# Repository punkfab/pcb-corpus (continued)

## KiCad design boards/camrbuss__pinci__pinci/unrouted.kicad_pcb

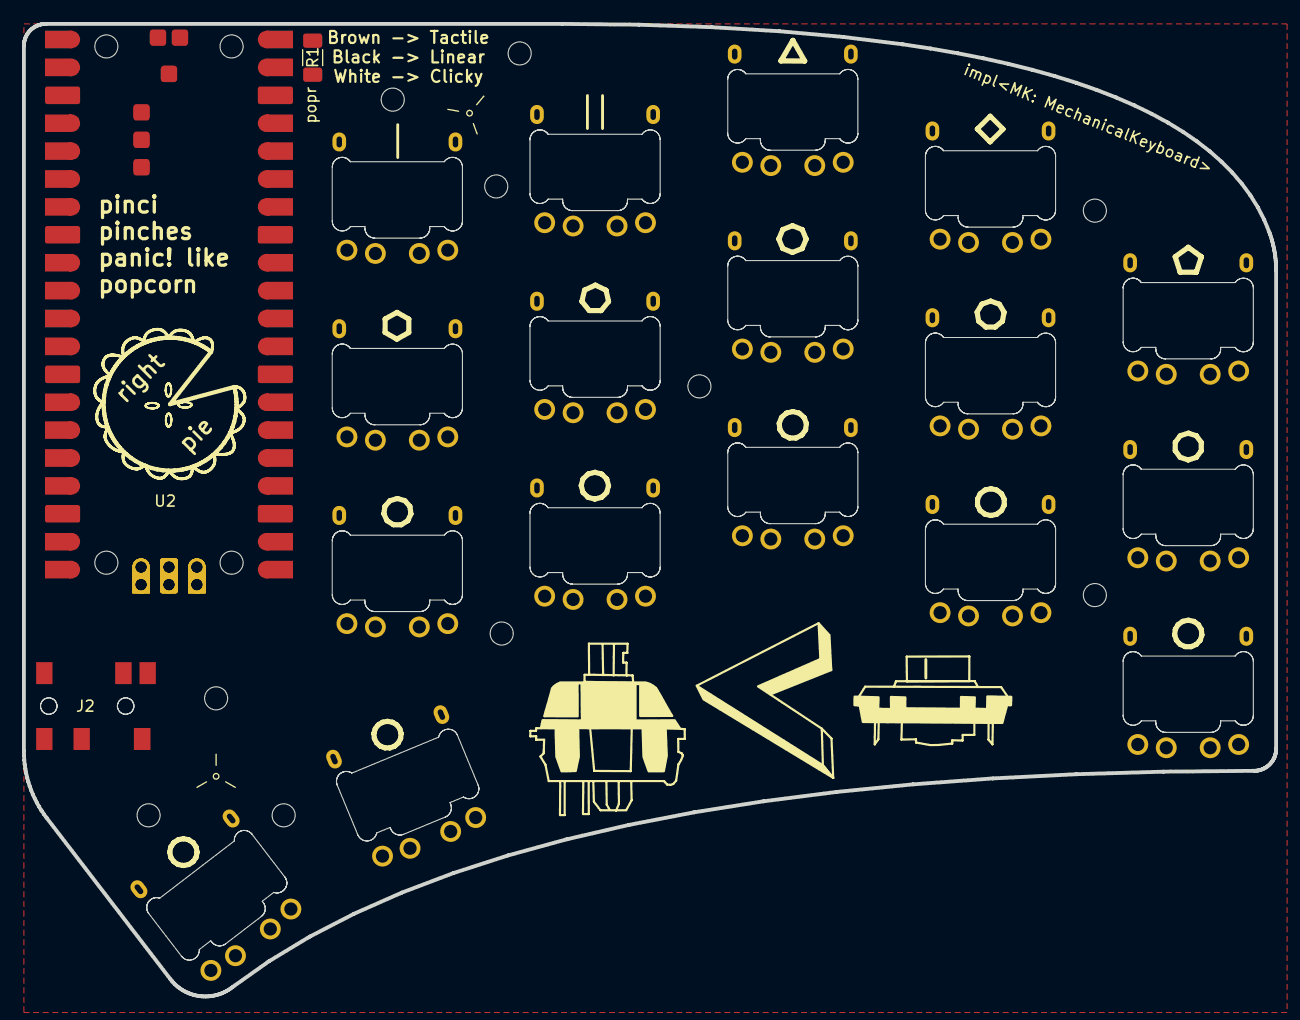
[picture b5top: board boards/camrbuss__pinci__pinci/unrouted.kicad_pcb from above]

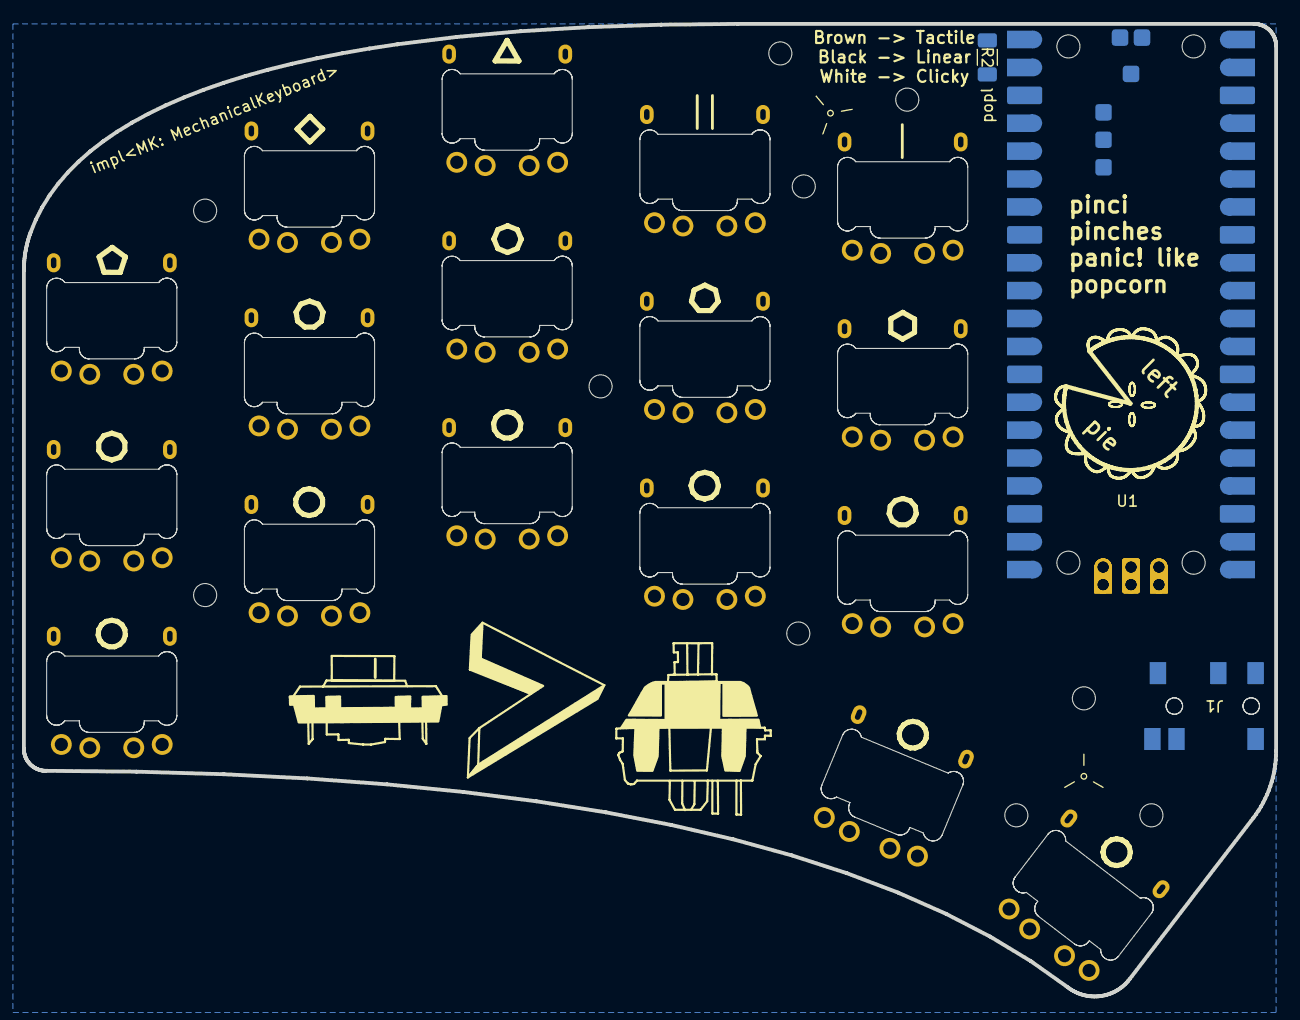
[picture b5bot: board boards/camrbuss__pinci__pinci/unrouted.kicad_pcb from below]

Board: 2 copper layers, 114.0 x 88.5 mm, 29 parts (5 on the bottom side), 42 nets, no tracks yet.

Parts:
H1, H2: MountingHole; 90611A112_Screw_Mount_Nut
H3, H4, H5, H6: MountingHole; M2_Hole
J1, J2: AudioJack4; TRRS_Socket_54-00177
R1, R2: 10k; R_1206_3216Metric_Pad1.30x1.75mm_HandSolder
SW1, SW2, SW3, SW4, SW5, SW6, SW7, SW8, SW9, SW10, SW11, SW12, SW13, SW14, SW15, SW16, SW17: SW_Push_Dual; Kailh_PG1232
U1, U2: PICO; raspberrypi_pico

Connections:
+3V3: R1.2, U1.36 (3V3), U2.36 (3V3)
GND: J1.T, J2.T, R2.1, SW1.2, SW1.4, SW2.2, SW2.4, SW3.2, SW3.4, SW4.2, SW4.4, SW5.2, SW5.4, SW6.2, SW6.4, SW7.2, SW7.4, SW8.2, SW8.4, SW9.2, SW9.4, SW10.2, SW10.4, SW11.2, SW11.4, SW12.2, SW12.4, SW13.2, SW13.4, SW14.2, SW14.4, SW15.2, SW15.4, SW16.2, SW16.4, SW17.2, SW17.4, U1.3 (GND), U1.8 (GND), U1.13 (GND), U1.18 (GND), U1.23 (GND), U1.28 (GND), U1.33 (AGND), U1.38 (GND), U1.D2 (GND), U2.3 (GND), U2.8 (GND), U2.13 (GND), U2.18 (GND), U2.23 (GND), U2.28 (GND), U2.33 (AGND), U2.38 (GND), U2.D2 (GND)
L1: SW1.3, U1.4 (GP2)
L2: SW2.3, U1.34 (GP28)
L3: SW3.3, U1.5 (GP3)
L4: SW4.3, U1.32 (GP27)
L5: SW5.3, U1.6 (GP4)
L6: SW6.3, U1.7 (GP5)
L7: SW7.3, U1.31 (GP26)
L8: SW8.3, U1.9 (GP6)
L9: SW9.3, U1.29 (GP22)
L10: SW10.3, U1.10 (GP7)
L11: SW11.3, U1.14 (GP10)
L12: SW12.3, U1.15 (GP11)
L13: SW13.3, U1.16 (GP12)
L14: SW14.3, U1.27 (GP21)
L15: SW15.3, U1.17 (GP13)
L16: SW16.3, U1.20 (GP15)
L17: SW17.3, U1.19 (GP14)
LR_ID: R1.1, R2.2, U1.2 (GP1), U2.2 (GP1)
L_RX: J1.S, U1.22 (GP17)
L_TX: J1.R2, U1.21 (GP16)
R1: SW1.1, U2.4 (GP2)
R2: SW2.1, U2.34 (GP28)
R3: SW3.1, U2.5 (GP3)
R4: SW4.1, U2.32 (GP27)
R5: SW5.1, U2.6 (GP4)
R6: SW6.1, U2.7 (GP5)
R7: SW7.1, U2.31 (GP26)
R8: SW8.1, U2.9 (GP6)
R9: SW9.1, U2.29 (GP22)
R10: SW10.1, U2.10 (GP7)
R11: SW11.1, U2.14 (GP10)
R12: SW12.1, U2.15 (GP11)
R13: SW13.1, U2.16 (GP12)
R14: SW14.1, U2.27 (GP21)
R15: SW15.1, U2.17 (GP13)
R16: SW16.1, U2.20 (GP15)
R17: SW17.1, U2.19 (GP14)
R_RX: J2.R2, U2.22 (GP17)
R_TX: J2.S, U2.21 (GP16)
VBUS: J1.R1, J2.R1, U1.39 (VSYS), U1.40 (VBUS), U2.39 (VSYS), U2.40 (VBUS)

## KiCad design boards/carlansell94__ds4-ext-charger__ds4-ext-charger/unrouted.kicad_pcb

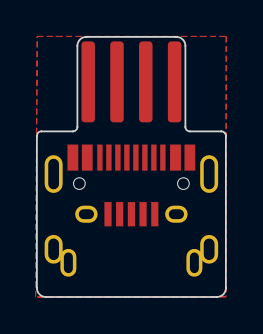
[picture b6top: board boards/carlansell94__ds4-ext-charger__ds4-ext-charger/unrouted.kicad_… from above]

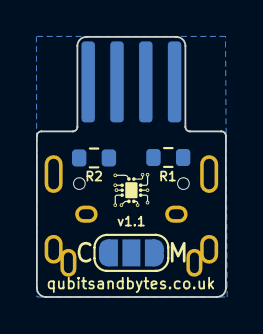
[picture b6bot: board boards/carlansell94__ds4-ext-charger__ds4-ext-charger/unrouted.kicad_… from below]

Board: 2 copper layers, 10.5 x 14.5 mm, 6 parts (3 on the bottom side), 6 nets, no tracks yet.

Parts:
J1: Conn_01x08_MountingPin; PS4 EXT
J2: USB_B_Micro; USB_Micro-B_Amphenol_10118194_Horizontal
J3: USB_C_Receptacle; USB_C_Receptacle_HRO_TYPE-C-31-M-12
JP1: SolderJumper_3_Open; SolderJumper-3_P1.3mm_Open_RoundedPad1.0x1.5mm_NumberLabels
R1, R2: 5.1k; R_0603_1608Metric

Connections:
/GND: J1.6 (Pin_1), J1.7 (Pin_2), J2.5 (GND), J2.6 (Shield), J3.A1 (GND), J3.A12 (GND), J3.B1 (GND), J3.B12 (GND), J3.S1 (SHIELD), R1.1, R2.1
unnamed: J1.12 (Pin_7), JP1.2 (C)
unnamed: J2.1 (VBUS), JP1.3 (B)
unnamed: J3.A4 (VBUS), J3.A9 (VBUS), J3.B4 (VBUS), J3.B9 (VBUS), JP1.1 (A)
unnamed: J3.A5 (CC1), R1.2
unnamed: J3.B5 (CC2), R2.2
